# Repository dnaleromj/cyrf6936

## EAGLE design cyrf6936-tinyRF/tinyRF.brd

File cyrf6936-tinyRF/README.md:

tinyRF
==================

Tiny PCB for a tiny, tiny receiver.
Shooting for 10x10mm
PCB antenna as per Cypress guidelines right now and is  not yet tuned.

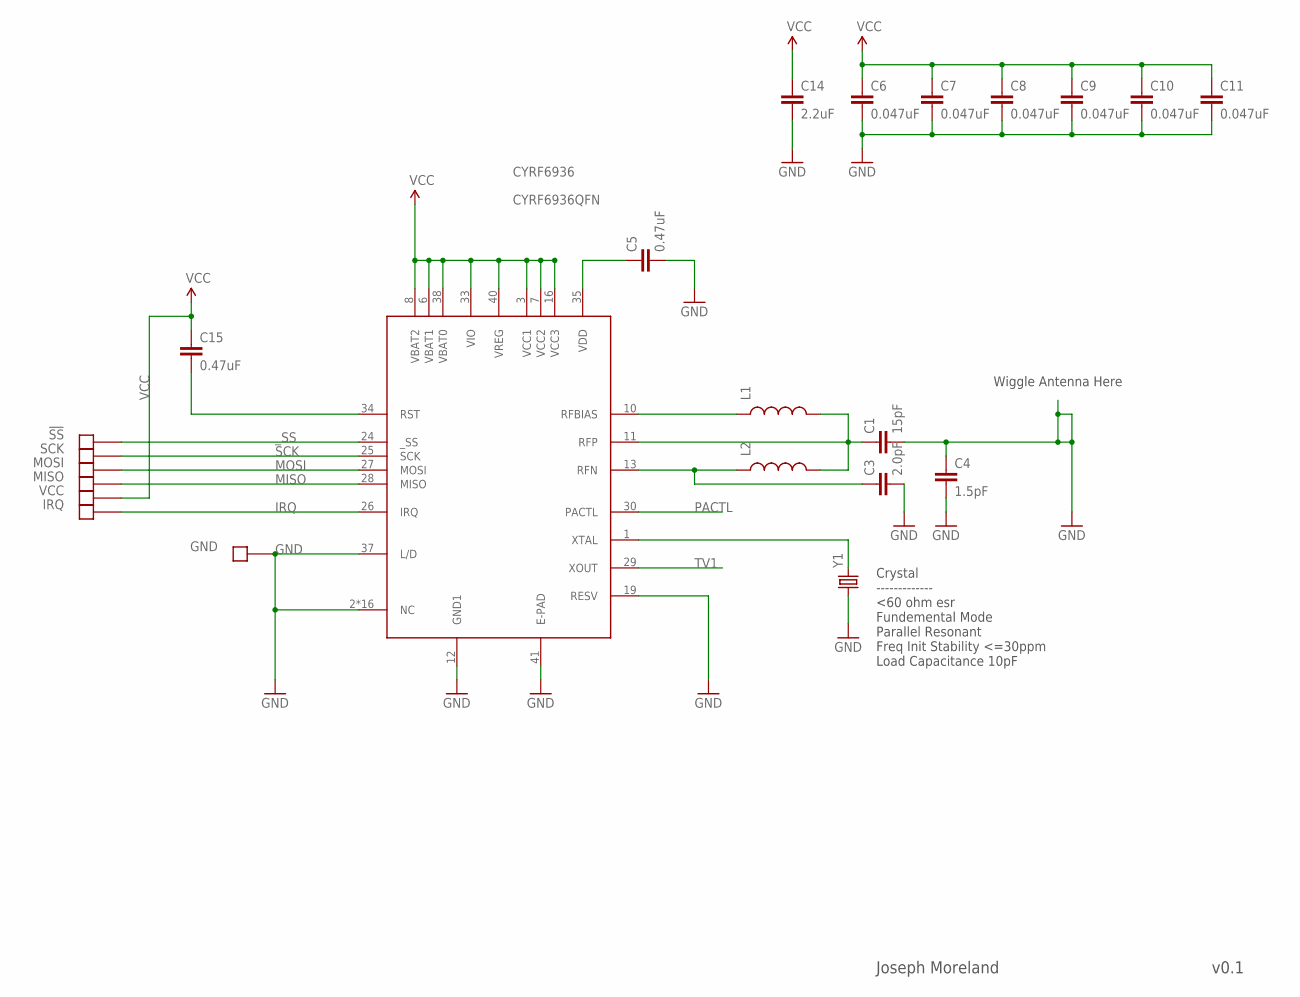
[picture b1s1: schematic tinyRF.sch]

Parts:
!SS: SOLDER_PADTH; 1X1_50MIL
C1: 15pF; 0402-CAP; PARTNO C0402C150J5GACTU
C3: 2.0pF; 0402-CAP; PARTNO C0402C209C5GACTU
C4: 1.5pF; 0402-CAP; PARTNO C0402C159B5GACTU
C5, C15: 0.47uF; 0402-CAP; PARTNO GRM155R60J474KE19D
C6, C7, C8, C9, C10, C11: 0.047uF; 0402-CAP; PARTNO 0402YD473KAT2A
C14: 2.2uF; 0805; PARTNO GRM21BR71A225KA01L
CYRF6936: CYRF6936QFN; QFN50P600X600X90-41N; PARTNO CYRF6936B-40LTXC
GND: SOLDER_PADTH; 1X1_50MIL
IRQ: SOLDER_PADTH; 1X1_50MIL
L1: INDUCTOR0603; 0603; PARTNO ELJ-RE22NGFA
L2: INDUCTOR0402; C0402; PARTNO ELJ-RF1N8DFB
MISO: SOLDER_PADTH; 1X1_50MIL
MOSI: SOLDER_PADTH; 1X1_50MIL
SCK: SOLDER_PADTH; 1X1_50MIL
VCC: SOLDER_PADTH; 1X1_50MIL
Y1: CRYSTAL5X3; CRYSTAL-SMD-5X3; PARTNO 7B-12.000MEEQ-T

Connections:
GND: C1.2, C3.2, C4.1, C4.2, C5.2, C6.2, C7.2, C8.2, C9.2, C10.2, C11.2, C14.2, CYRF6936.2 (NC), CYRF6936.4 (NC), CYRF6936.5 (NC), CYRF6936.9 (NC), CYRF6936.12 (GND1), CYRF6936.14 (NC), CYRF6936.15 (NC), CYRF6936.17 (NC), CYRF6936.18 (NC), CYRF6936.19 (RESV), CYRF6936.20 (NC), CYRF6936.21 (NC), CYRF6936.22 (NC), CYRF6936.23 (NC), CYRF6936.31 (NC), CYRF6936.32 (NC), CYRF6936.36 (NC), CYRF6936.37 (L/D), CYRF6936.39 (NC), CYRF6936.41 (E-PAD), GND.1, Y1.1
IRQ: CYRF6936.26 (IRQ), IRQ.1
MISO: CYRF6936.28 (MISO), MISO.1
MOSI: CYRF6936.27 (MOSI), MOSI.1
unnamed: CYRF6936.1 (XTAL), Y1.3 (2)
PACTL: CYRF6936.30 (PACTL)
RFBIAS: CYRF6936.10 (RFBIAS), L1.1
RFN: C3.1, CYRF6936.13 (RFN), L2.1
RFP: C1.1, CYRF6936.11 (RFP), L1.2, L2.2
RST: C15.2, CYRF6936.34 (RST)
SCK: CYRF6936.25 (SCK), SCK.1
TV1: CYRF6936.29 (XOUT)
VCC: C6.1, C7.1, C8.1, C9.1, C10.1, C11.1, C14.1, C15.1, CYRF6936.3 (VCC1), CYRF6936.6 (VBAT1), CYRF6936.7 (VCC2), CYRF6936.8 (VBAT2), CYRF6936.16 (VCC3), CYRF6936.33 (VIO), CYRF6936.38 (VBAT0), CYRF6936.40 (VREG), VCC.1
VDD: C5.1, CYRF6936.35 (VDD)
_SS: !SS.1, CYRF6936.24 (_SS)

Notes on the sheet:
Wiggle Antenna Here
Crystal ------------- <60 ohm esr Fundemental Mode Parallel Resonant Freq Init Stability <=30ppm Load Capacitance 10pF
Joseph Moreland
v0.1

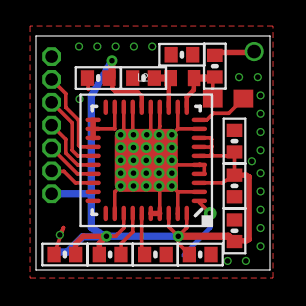
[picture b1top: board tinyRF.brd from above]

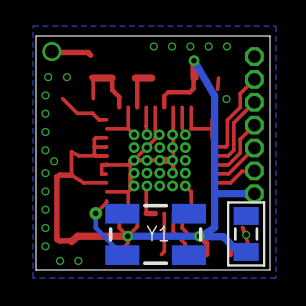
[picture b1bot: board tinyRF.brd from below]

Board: 2 copper layers, 13.0 x 13.0 mm, 23 parts (3 on the bottom side), 13 nets.

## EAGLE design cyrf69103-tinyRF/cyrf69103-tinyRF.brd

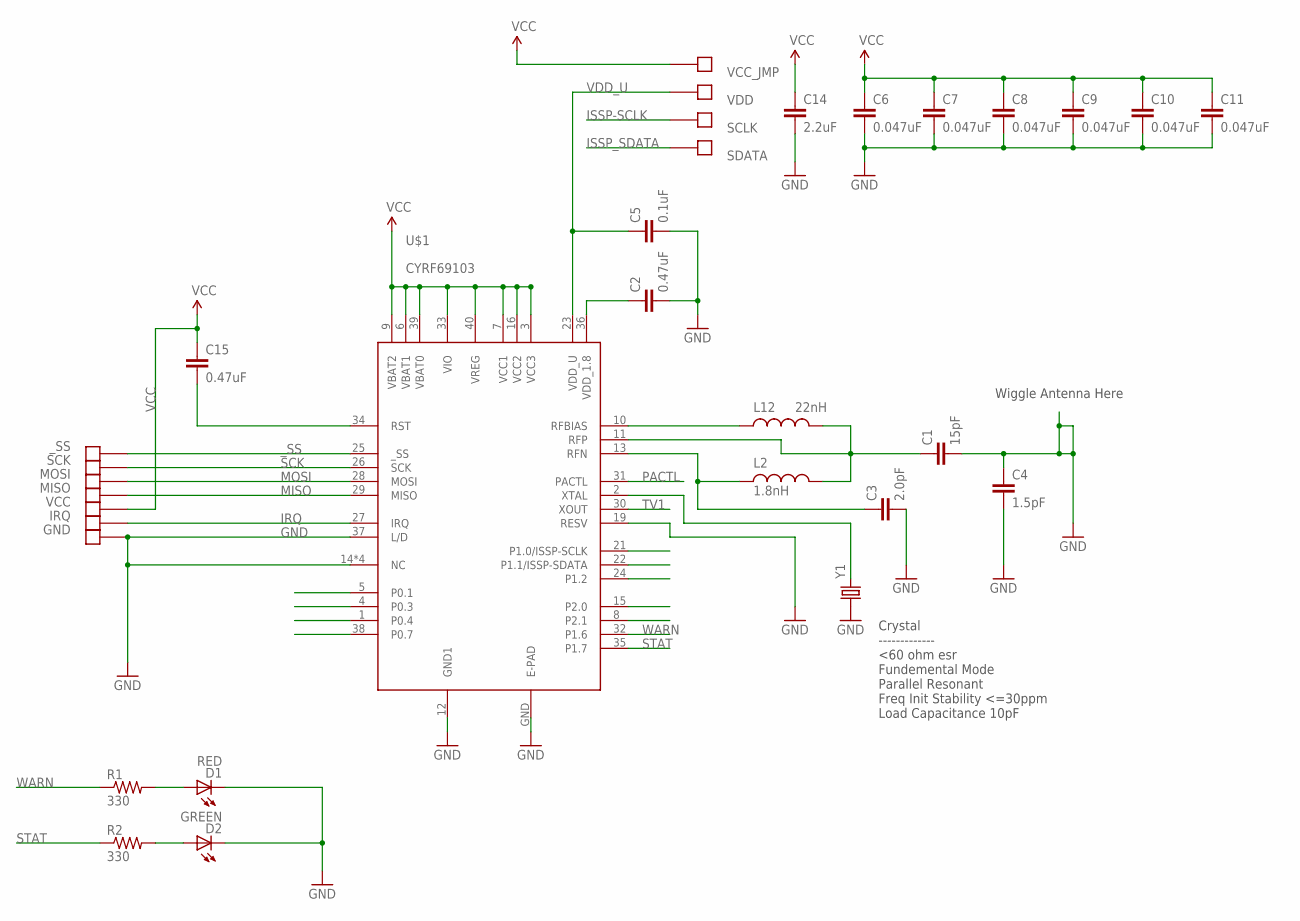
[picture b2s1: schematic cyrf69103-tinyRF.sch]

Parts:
C1: 15pF; 0402-CAP; PARTNO C0402C150J5GACTU
C2, C15: 0.47uF; 0402-CAP; PARTNO GRM155R60J474KE19D
C3: 2.0pF; 0402-CAP; PARTNO C0402C209C5GACTU
C4: 1.5pF; 0402-CAP; PARTNO C0402C159B5GACTU
C5: 0.1uF; 0402-CAP; PARTNO GRM155R60J474KE19D
C6, C7, C8, C9, C10, C11: 0.047uF; 0402-CAP; PARTNO 0402YD473KAT2A
C14: 2.2uF; 0805; PARTNO GRM21BR71A225KA01L
D1: RED; LED-0603; PARTNO LTST-C191TBKT
D2: GREEN; LED-0603; PARTNO LTST-C190KGKT
GND: SOLDER_PAD.05X.05; SOLDER_PAD_.05X.05
IRQ: SOLDER_PAD.05X.05; SOLDER_PAD_.05X.05
L2: 1.8nH; C0402; PARTNO ELJ-RF1N8DFB
L12: 22nH; 0603; PARTNO ELJ-RE22NGFA
MISO: SOLDER_PAD.05X.05; SOLDER_PAD_.05X.05
MOSI: SOLDER_PAD.05X.05; SOLDER_PAD_.05X.05
R1, R2: 330; 0402-RES; PARTNO CRCW0402330RJNED
SCK: SOLDER_PAD.05X.05; SOLDER_PAD_.05X.05
SCLK: SOLDER_PAD.05X.05; SOLDER_PAD_.05X.05
SDATA: SOLDER_PAD.05X.05; SOLDER_PAD_.05X.05
U$1: CYRF69103; QFN40; PARTNO CYRF69103-40LFXC
VCC: SOLDER_PAD.05X.05; SOLDER_PAD_.05X.05
VCC_JMP: SOLDER_PAD.05X.05; SOLDER_PAD_.05X.05
VDD: SOLDER_PAD.05X.05; SOLDER_PAD_.05X.05
Y1: CRYSTAL5X3; CRYSTAL-SMD-5X3; PARTNO 7B-12.000MEEQ-T
_SS: SOLDER_PAD.05X.05; SOLDER_PAD_.05X.05

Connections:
GND: C1.2, C2.2, C3.2, C4.1, C4.2, C5.2, C6.2, C7.2, C8.2, C9.2, C10.2, C11.2, C14.2, D1.C, D2.C, GND.P$1, U$1.12 (GND1), U$1.14 (NC), U$1.17 (NC), U$1.18 (NC), U$1.20 (NC), U$1.37 (L/D), U$1.GND (E-PAD), Y1.1
IRQ: IRQ.P$1, U$1.27 (IRQ)
ISSP-SCLK: SCLK.P$1, U$1.21 (P1.0/ISSP-SCLK)
ISSP_SDATA: SDATA.P$1, U$1.22 (P1.1/ISSP-SDATA)
MISO: MISO.P$1, U$1.29 (MISO)
MOSI: MOSI.P$1, U$1.28 (MOSI)
unnamed: D1.A, R1.2
unnamed: U$1.2 (XTAL), Y1.3 (2)
unnamed: D2.A, R2.2
PACTL: U$1.31 (PACTL)
RFBIAS: L12.1, U$1.10 (RFBIAS)
RFN: C3.1, L2.1, U$1.13 (RFN)
RFP: C1.1, L2.2, L12.2, U$1.11 (RFP)
RST: C15.2, U$1.34 (RST)
SCK: SCK.P$1, U$1.26 (SCK)
STAT: R2.1, U$1.35 (P1.7)
VCC: C6.1, C7.1, C8.1, C9.1, C10.1, C11.1, C14.1, C15.1, U$1.3 (VCC3), U$1.6 (VBAT1), U$1.7 (VCC1), U$1.9 (VBAT2), U$1.16 (VCC2), U$1.33 (VIO), U$1.39 (VBAT0), U$1.40 (VREG), VCC.P$1, VCC_JMP.P$1
VDD_1.8: C2.1, U$1.36 (VDD_1.8)
VDD_U: C5.1, U$1.23 (VDD_U), VDD.P$1
WARN: R1.1, U$1.32 (P1.6)
_SS: U$1.25 (_SS), _SS.P$1

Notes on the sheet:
Wiggle Antenna Here
Crystal ------------- <60 ohm esr Fundemental Mode Parallel Resonant Freq Init Stability <=30ppm Load Capacitance 10pF

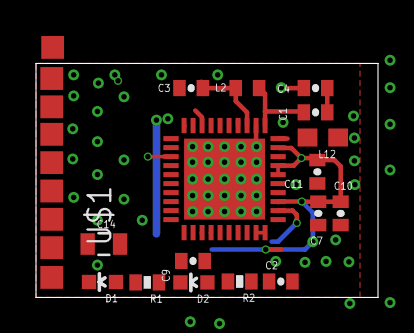
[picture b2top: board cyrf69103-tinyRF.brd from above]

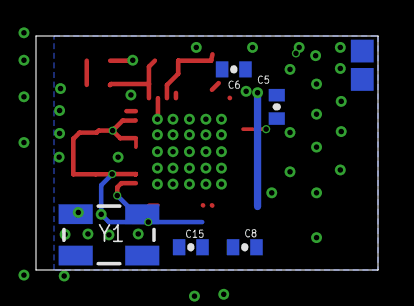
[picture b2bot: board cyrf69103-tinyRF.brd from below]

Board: 2 copper layers, 19.0 x 13.0 mm, 32 parts (7 on the bottom side), 20 nets.

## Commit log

2013-04-18 Initial upload
2013-04-19 Panel add
    Panel generation added with fab drawings, etc.
2013-04-19 broke down into multiple boards a Break out Board and a production oriented board
2013-04-20 restructured to try to keep track of various production files. also, tuned panel for vscore.
    restructured to try to keep track of various production files.
    tuned panel for vscore.
    Cleaned up cyrf6936-bob to mask solder mask from the antenna area.
2013-04-23 Add cyrf69103 (MCU + radio) break out and tiny, neither finished.
2013-04-23 Added revision and author
2013-05-15 Updated cyrf6936 footprint, corrected cyrf6936 bob and tiny board.
2013-05-15 Screwed up that last commit. this update include changes to the production gerber folders. Adds hackvana to the cyrf6936-BoB and cleans up the fab notes a bit. Still need to standardize and parameter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

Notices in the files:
parts and their libraries:
SparkFun-Passives: Licensing: CC v3.0 Share-Alike You are welcome to use this library for commercial purposes.
